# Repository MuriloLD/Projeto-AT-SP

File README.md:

# Projeto-AT-SP
Source code and instructions needed for constructing AntTruck and SuperTruck. Both mobile robots conected to Internet.

For more information please download the documentation [here](https://github.com/MuriloLD/Projeto-AT-SP/blob/master/Documenta%C3%A7%C3%A3o_Projeto_ATSP.pdf).

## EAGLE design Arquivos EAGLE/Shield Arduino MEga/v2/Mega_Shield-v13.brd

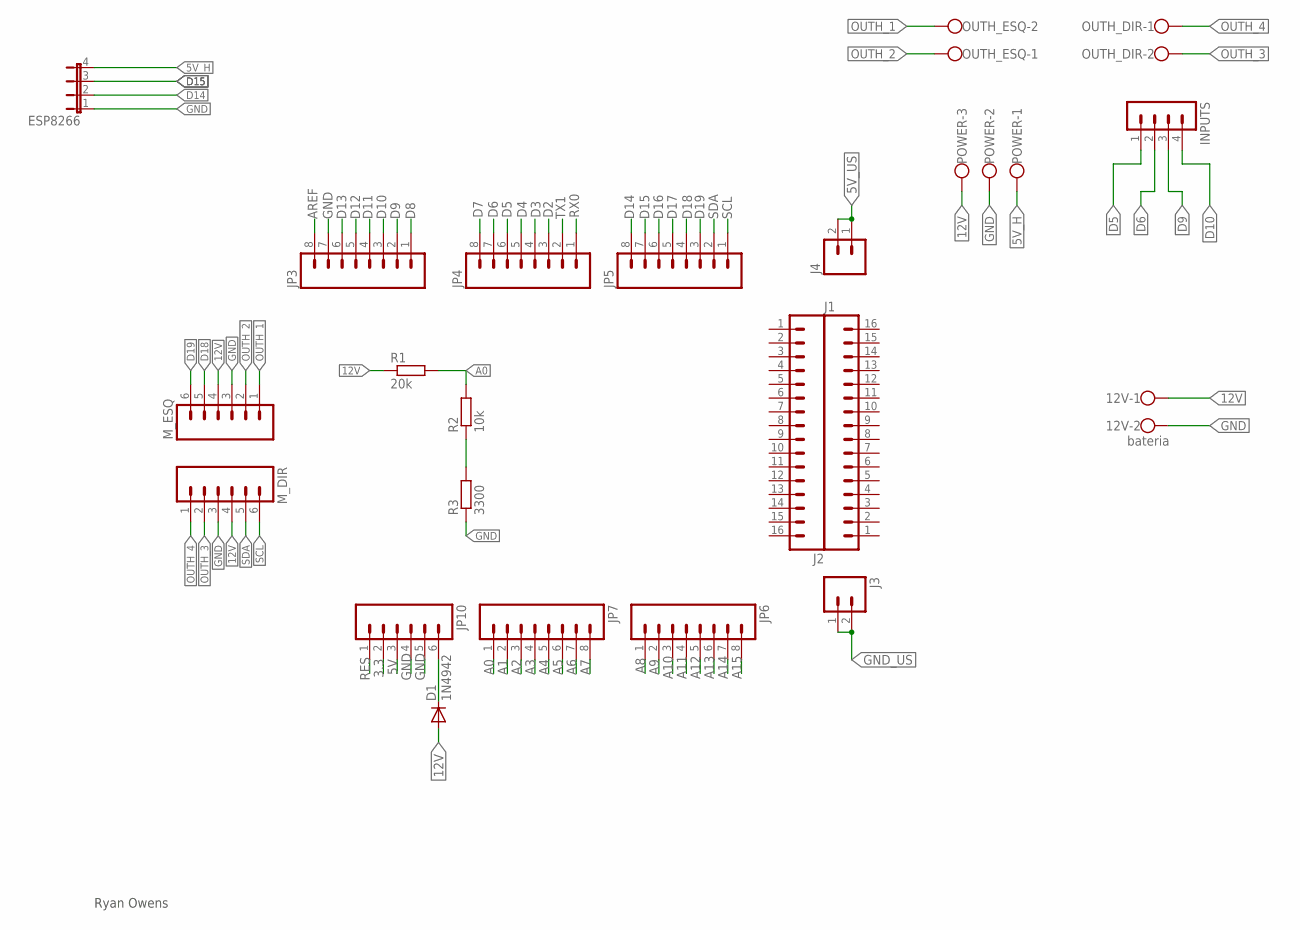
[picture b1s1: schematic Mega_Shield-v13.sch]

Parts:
12V: bateria; W237-102
D1: 1N4942; DO41-10
ESP8266: JP4E; JP4
INPUTS: MA04-1
J1, J2: M16LOCK; 1X16_LOCK
J3, J4: M02LOCK; 1X02_LOCK
JP3, JP4, JP5, JP6, JP7: M08LOCK; 1X08_LOCK
JP10: M06LOCK; 1X06_LOCK
M_DIR: M06LOCK; 1X06_LOCK
M_ESQ: M06LOCK; 1X06_LOCK
OUTH_DIR: W237-102
OUTH_ESQ: W237-102
POWER: W237-103
R1: 20k; 0207/10
R2: 10k; 0207/10
R3: 3300; 0207/10

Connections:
3.3: JP10.2
5V: JP10.3
5V_H: ESP8266.4, POWER.1
5V_US: J4.1, J4.2
12V: 12V.1, D1.A, M_DIR.4, M_ESQ.4, POWER.3, R1.1
A0: JP7.1, R1.2, R2.2
A1: JP7.2
A2: JP7.3
A3: JP7.4
A4: JP7.5
A5: JP7.6
A6: JP7.7
A7: JP7.8
A8: JP6.1
A9: JP6.2
A10: JP6.3
A11: JP6.4
A12: JP6.5
A13: JP6.6
A14: JP6.7
A15: JP6.8
AREF: JP3.8
D2: JP4.3
D3: JP4.4
D4: JP4.5
D5: INPUTS.1, JP4.6
D6: INPUTS.2, JP4.7
D7: JP4.8
D8: JP3.1
D9: INPUTS.3, JP3.2
D10: INPUTS.4, JP3.3
D11: JP3.4
D12: JP3.5
D13: JP3.6
D14: ESP8266.2, JP5.8
D15: ESP8266.3, JP5.7
D16: JP5.6
D17: JP5.5
D18: JP5.4, M_ESQ.5
D19: JP5.3, M_ESQ.6
GND: 12V.2, ESP8266.1, JP3.7, JP10.4, JP10.5, M_DIR.3, M_ESQ.3, POWER.2, R3.1
GND_US: J3.1, J3.2
unnamed: R2.1, R3.2
unnamed: D1.C, JP10.6
OUTH_1: M_ESQ.1, OUTH_ESQ.2
OUTH_2: M_ESQ.2, OUTH_ESQ.1
OUTH_3: M_DIR.2, OUTH_DIR.2
OUTH_4: M_DIR.1, OUTH_DIR.1
RES: JP10.1
RX0: JP4.1
SCL: JP5.1, M_DIR.6
SDA: JP5.2, M_DIR.5
TX1: JP4.2

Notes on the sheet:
Ryan Owens

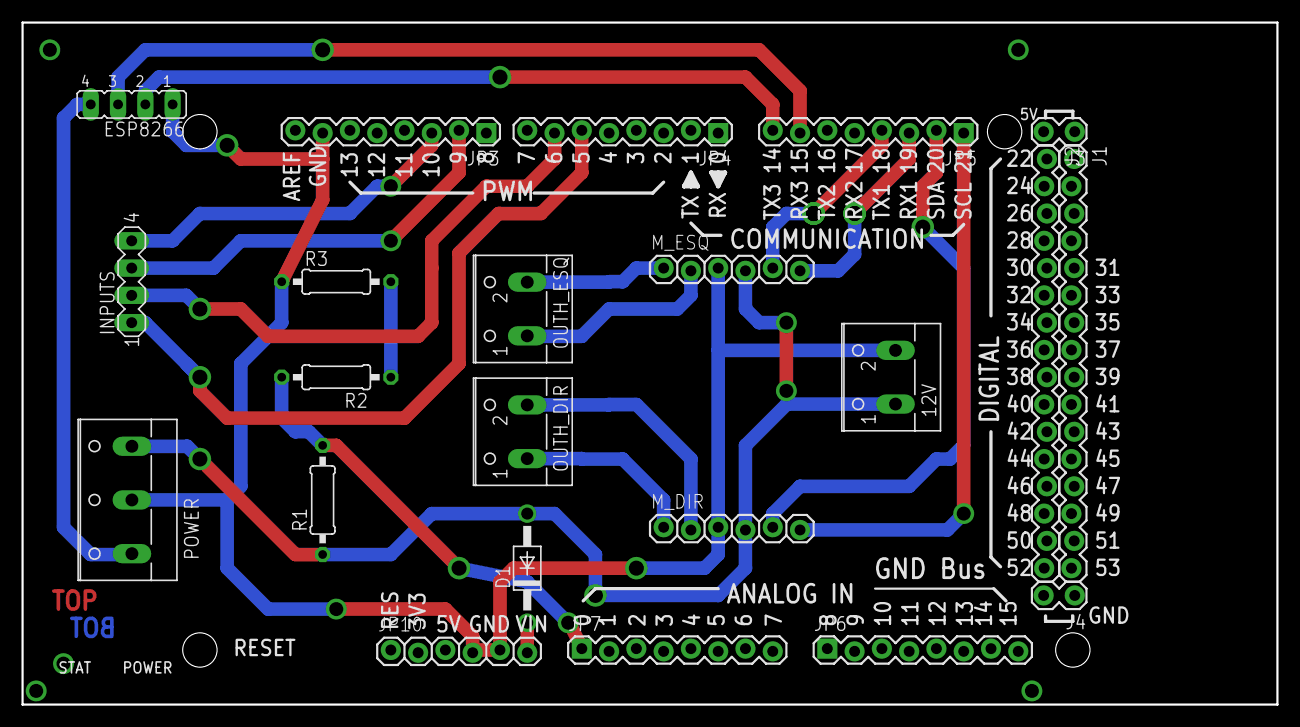
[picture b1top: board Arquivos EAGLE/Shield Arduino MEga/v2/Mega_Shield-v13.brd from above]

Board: 2 copper layers, 116.8 x 63.5 mm, 22 parts (0 on the bottom side), 22 nets.

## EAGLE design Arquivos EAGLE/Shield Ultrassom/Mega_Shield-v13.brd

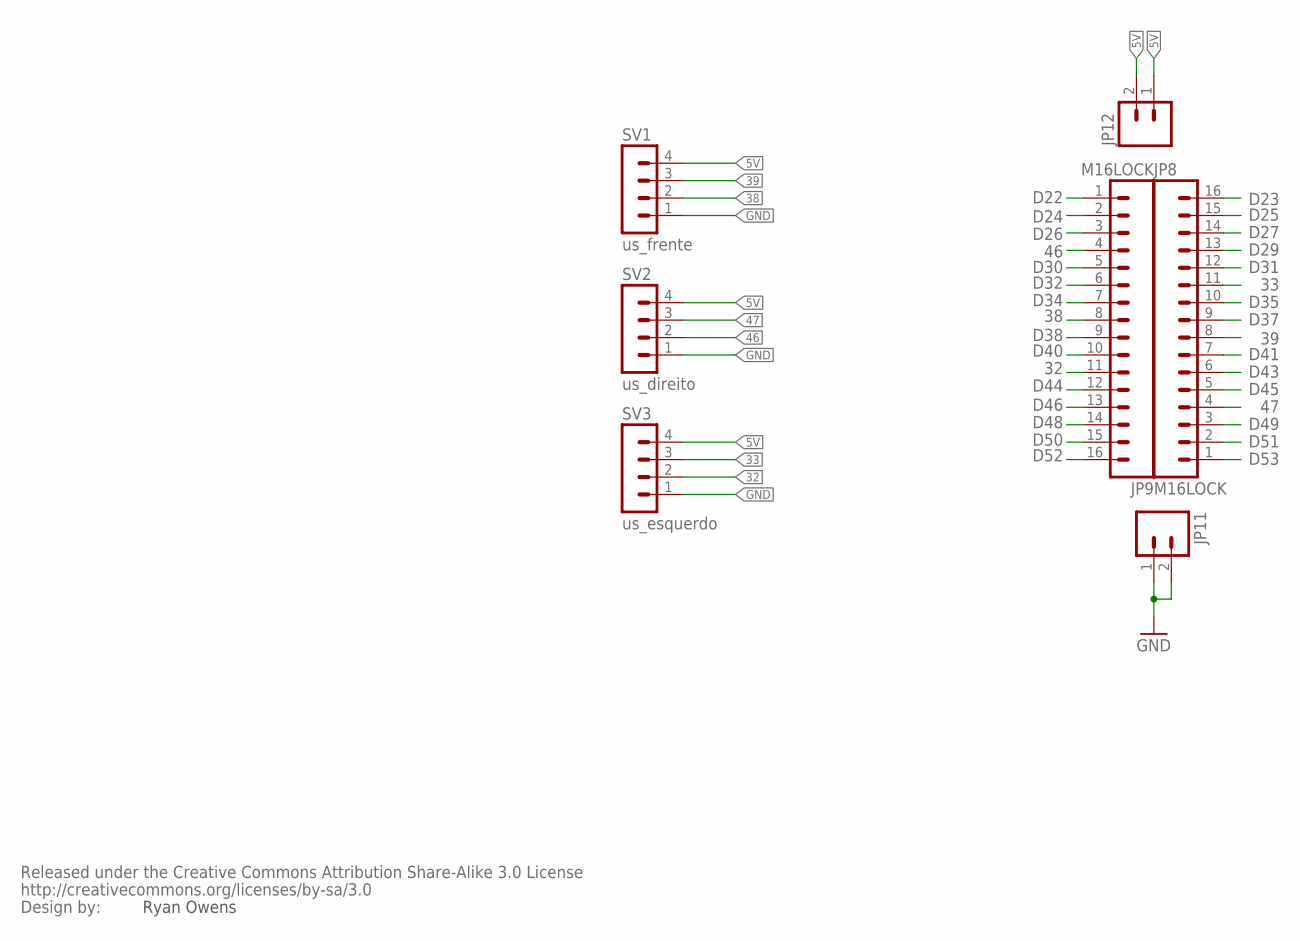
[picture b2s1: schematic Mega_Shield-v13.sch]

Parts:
JP8, JP9: M16LOCK; 1X16_LOCK
JP11, JP12: M02LOCK; 1X02_LOCK
SV1: us_frente; MA04-1
SV2: us_direito; MA04-1
SV3: us_esquerdo; MA04-1
U$2: CREATIVE_COMMONS

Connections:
5V: JP12.1, JP12.2, SV1.4, SV2.4, SV3.4
32: JP9.11, SV3.2
33: JP8.11, SV3.3
38: JP9.8, SV1.2
39: JP8.8, SV1.3
46: JP9.4, SV2.2
47: JP8.4, SV2.3
D22: JP9.1
D23: JP8.16
D24: JP9.2
D25: JP8.15
D26: JP9.3
D27: JP8.14
D29: JP8.13
D30: JP9.5
D31: JP8.12
D32: JP9.6
D34: JP9.7
D35: JP8.10
D37: JP8.9
D38: JP9.9
D40: JP9.10
D41: JP8.7
D43: JP8.6
D44: JP9.12
D45: JP8.5
D46: JP9.13
D48: JP9.14
D49: JP8.3
D50: JP9.15
D51: JP8.2
D52: JP9.16
D53: JP8.1
GND: JP11.1, JP11.2, SV1.1, SV2.1, SV3.1

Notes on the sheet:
Ryan Owens

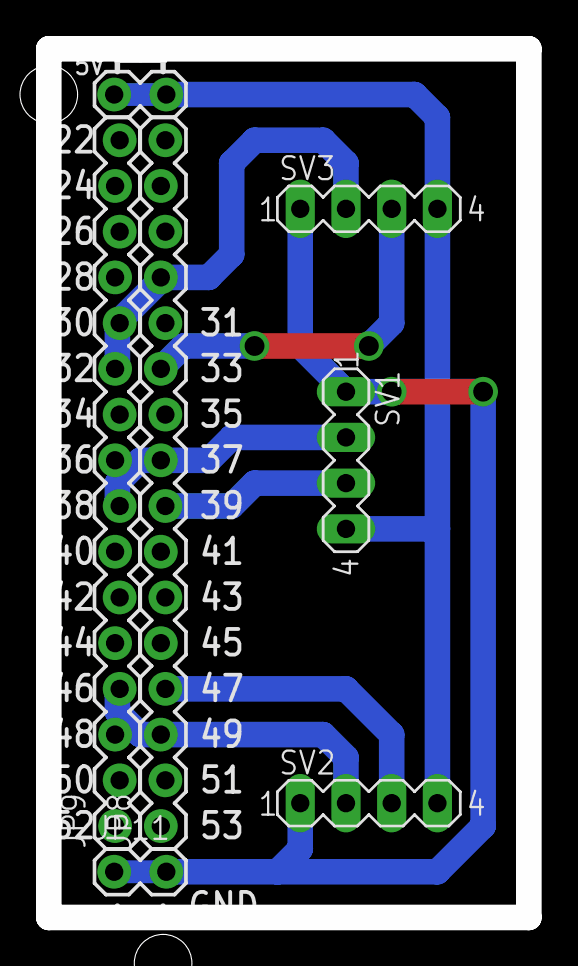
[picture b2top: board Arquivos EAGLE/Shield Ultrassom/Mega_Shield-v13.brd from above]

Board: 2 copper layers, 26.7 x 48.3 mm, 8 parts (0 on the bottom side), 8 nets.

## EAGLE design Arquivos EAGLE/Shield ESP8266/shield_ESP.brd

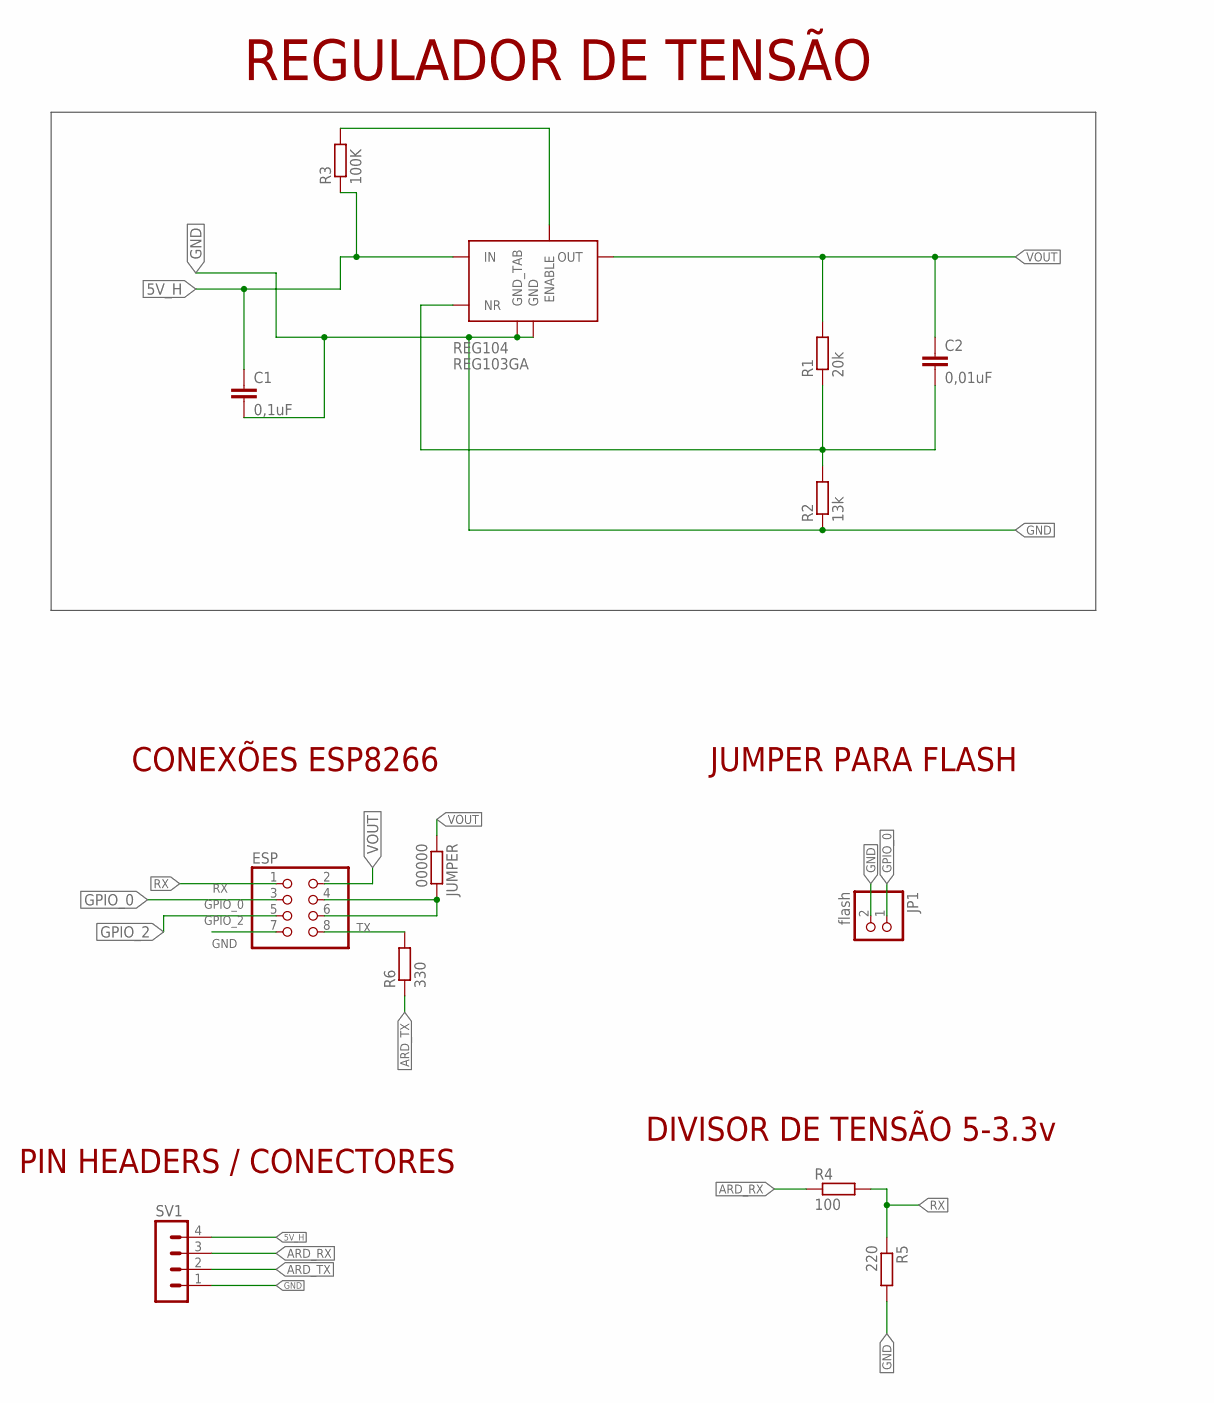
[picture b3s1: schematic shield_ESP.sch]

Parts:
C1: 0,1uF; C025-025X050
C2: 0,01uF; C025-025X050
ESP: PINHD-2X4; 2X04
JP1: flash; 1X02/90
JUMPER: 00000; 0207/7
R1: 20k; 0207/7
R2: 13k; 0207/7
R3: 100K; 0207/7
R4: 100; 0207/7
R5: 220; 0207/7
R6: 330; 0207/7
REG104: REG103GA; SOT223-5
SV1: MA04-1

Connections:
5V_H: C1.1, R3.1, REG104.1 (IN), SV1.4
ARD_RX: R4.1, SV1.3
ARD_TX: R6.1, SV1.2
GND: C1.2, ESP.7, JP1.2, R2.1, R5.2, REG104.3 (GND), REG104.TAB (GND_TAB), SV1.1
GPIO_0: ESP.3, JP1.1
GPIO_2: ESP.5
unnamed: ESP.4, ESP.6, JUMPER.2
unnamed: C2.2, R1.1, R2.2, REG104.4 (NR)
unnamed: R3.2, REG104.5 (ENABLE)
RX: ESP.1, R4.2, R5.1
TX: ESP.8, R6.2
VOUT: C2.1, ESP.2, JUMPER.1, R1.2, REG104.2 (OUT)

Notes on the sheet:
REGULADOR DE TENSÃO
PIN HEADERS / CONECTORES
DIVISOR DE TENSÃO 5-3.3v
CONEXÕES ESP8266
JUMPER PARA FLASH

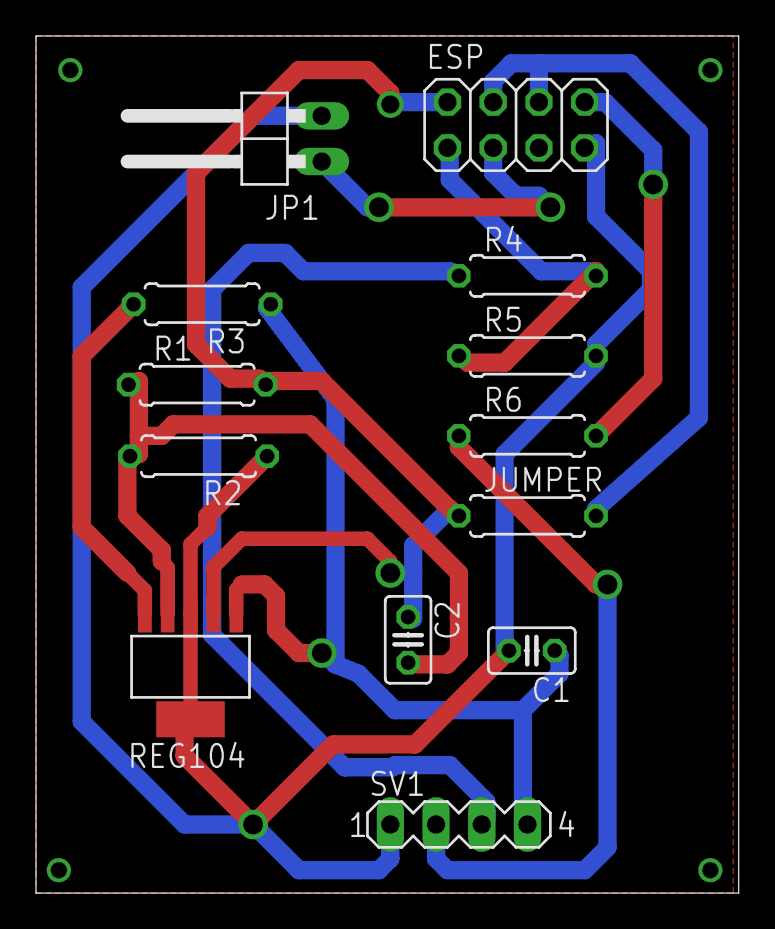
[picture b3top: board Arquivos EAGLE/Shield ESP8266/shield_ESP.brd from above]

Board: 2 copper layers, 39.0 x 47.6 mm, 13 parts (0 on the bottom side), 11 nets.

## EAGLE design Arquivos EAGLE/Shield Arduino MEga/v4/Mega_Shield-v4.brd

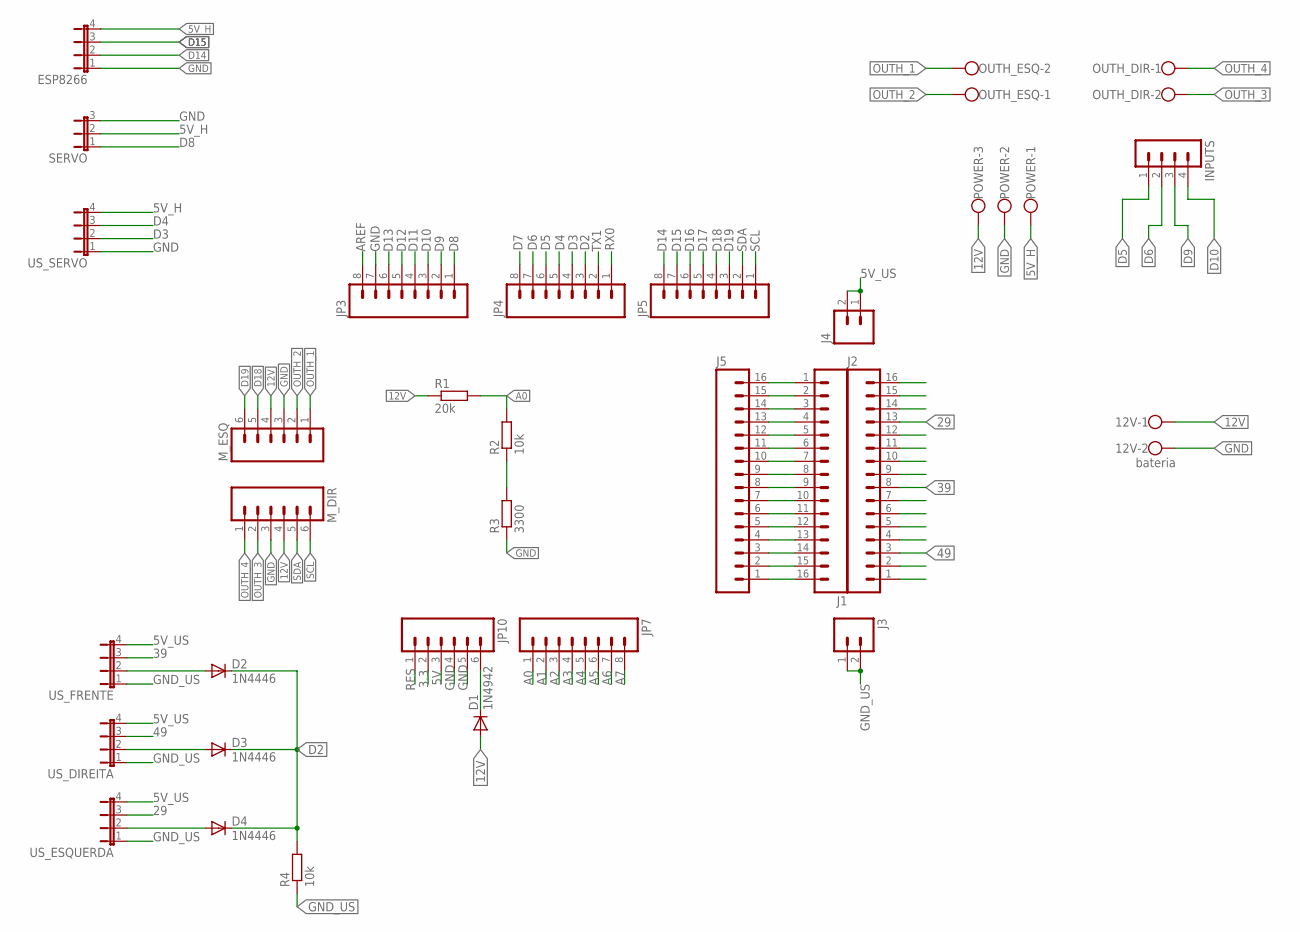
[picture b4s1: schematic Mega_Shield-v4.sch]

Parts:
12V: bateria; W237-102
D1: 1N4942; DO41-10
D2, D3, D4: 1N4446; DO35-10
ESP8266: JP4E; JP4
INPUTS: MA04-1
J1, J2, J5: M16LOCK; 1X16_LOCK
J3, J4: M02LOCK; 1X02_LOCK
JP3, JP4, JP5, JP7: M08LOCK; 1X08_LOCK
JP10: M06LOCK; 1X06_LOCK
M_DIR: M06LOCK; 1X06_LOCK
M_ESQ: M06LOCK; 1X06_LOCK
OUTH_DIR: W237-102
OUTH_ESQ: W237-102
POWER: W237-103
R1: 20k; 0207/10
R2, R4: 10k; 0207/10
R3: 3300; 0207/10
SERVO: JP2W
US_DIREITA: JP4E; JP4
US_ESQUERDA: JP4E; JP4
US_FRENTE: JP4E; JP4
US_SERVO: JP4E; JP4

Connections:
3.3: JP10.2
5V: JP10.3
5V_H: ESP8266.4, POWER.1, SERVO.2, US_SERVO.4
5V_US: J4.1, J4.2, US_DIREITA.4, US_ESQUERDA.4, US_FRENTE.4
12V: 12V.1, D1.A, M_DIR.4, M_ESQ.4, POWER.3, R1.1
29: J2.13, US_ESQUERDA.3
39: J2.8, US_FRENTE.3
49: J2.3, US_DIREITA.3
A0: JP7.1, R1.2, R2.2
A1: JP7.2
A2: JP7.3
A3: JP7.4
A4: JP7.5
A5: JP7.6
A6: JP7.7
A7: JP7.8
AREF: JP3.8
D2: D2.C, D3.C, D4.C, JP4.3, R4.2
D3: JP4.4, US_SERVO.2
D4: JP4.5, US_SERVO.3
D5: INPUTS.1, JP4.6
D6: INPUTS.2, JP4.7
D7: JP4.8
D8: JP3.1, SERVO.1
D9: INPUTS.3, JP3.2
D10: INPUTS.4, JP3.3
D11: JP3.4
D12: JP3.5
D13: JP3.6
D14: ESP8266.2, JP5.8
D15: ESP8266.3, JP5.7
D16: JP5.6
D17: JP5.5
D18: JP5.4, M_ESQ.5
D19: JP5.3, M_ESQ.6
GND: 12V.2, ESP8266.1, JP3.7, JP10.4, JP10.5, M_DIR.3, M_ESQ.3, POWER.2, R3.1, SERVO.3, US_SERVO.1
GND_US: J3.1, J3.2, R4.1, US_DIREITA.1, US_ESQUERDA.1, US_FRENTE.1
unnamed: R2.1, R3.2
unnamed: D1.C, JP10.6
unnamed: D2.A, US_FRENTE.2
unnamed: J1.16, J5.1
unnamed: D3.A, US_DIREITA.2
unnamed: J1.15, J5.2
unnamed: J1.14, J5.3
unnamed: J1.13, J5.4
unnamed: D4.A, US_ESQUERDA.2
unnamed: J1.12, J5.5
unnamed: J1.11, J5.6
unnamed: J1.10, J5.7
unnamed: J1.9, J5.8
unnamed: J1.8, J5.9
unnamed: J1.7, J5.10
unnamed: J1.6, J5.11
unnamed: J1.5, J5.12
unnamed: J1.4, J5.13
unnamed: J1.3, J5.14
unnamed: J1.2, J5.15
unnamed: J1.1, J5.16
OUTH_1: M_ESQ.1, OUTH_ESQ.2
OUTH_2: M_ESQ.2, OUTH_ESQ.1
OUTH_3: M_DIR.2, OUTH_DIR.2
OUTH_4: M_DIR.1, OUTH_DIR.1
RES: JP10.1
RX0: JP4.1
SCL: JP5.1, M_DIR.6
SDA: JP5.2, M_DIR.5
TX1: JP4.2

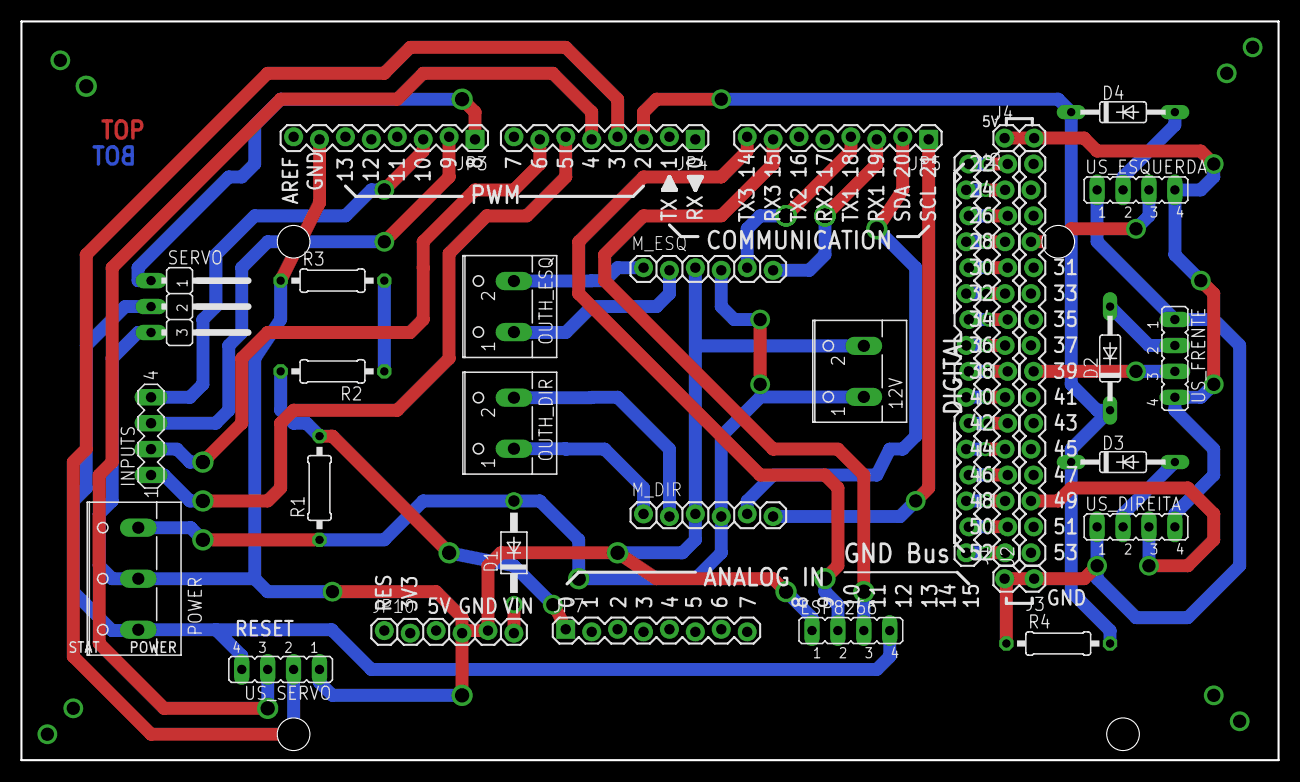
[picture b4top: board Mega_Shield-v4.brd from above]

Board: 2 copper layers, 123.2 x 72.4 mm, 31 parts (0 on the bottom side), 48 nets.

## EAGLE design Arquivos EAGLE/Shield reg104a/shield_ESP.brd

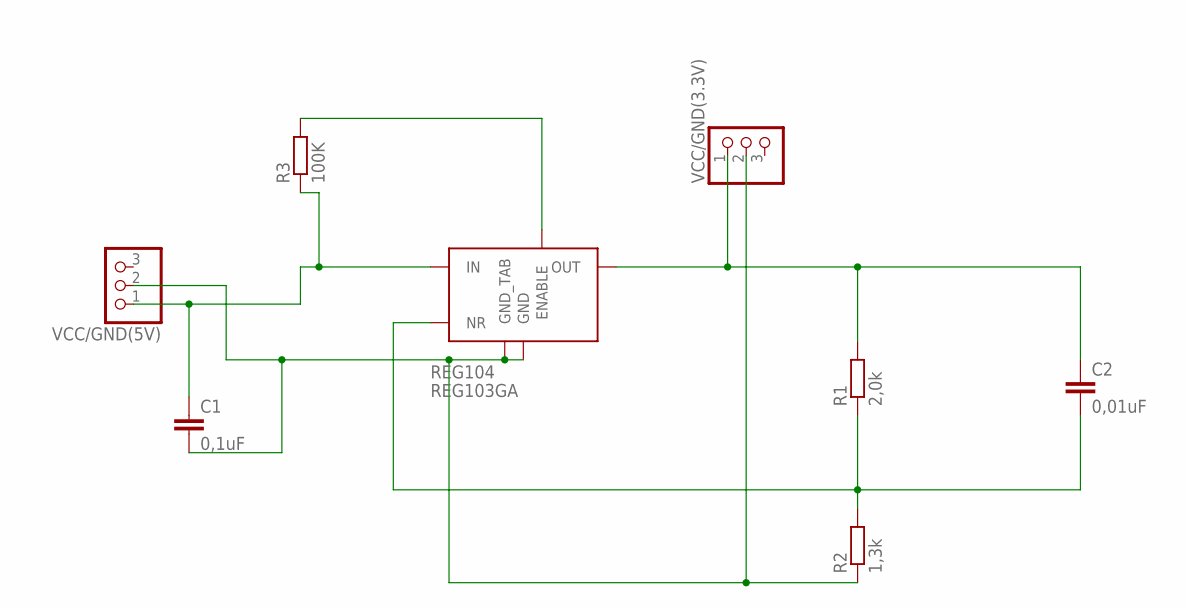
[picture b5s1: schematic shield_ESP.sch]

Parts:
C1: 0,1uF; C025-025X050
C2: 0,01uF; C025-025X050
R1: 2,0k; 0207/7
R2: 1,3k; 0207/7
R3: 100K; 0207/7
REG104: REG103GA; SOT223-5
VCC/GND(3.3V), VCC/GND(5V): PINHD-1X3/90; 1X03/90

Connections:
GOUT: C1.2, R2.1, REG104.3 (GND), REG104.TAB (GND_TAB), VCC/GND(3.3V).2, VCC/GND(5V).2
unnamed: C1.1, R3.1, REG104.1 (IN), VCC/GND(5V).1
unnamed: C2.2, R1.1, R2.2, REG104.4 (NR)
unnamed: R3.2, REG104.5 (ENABLE)
VOUT: C2.1, R1.2, REG104.2 (OUT), VCC/GND(3.3V).1

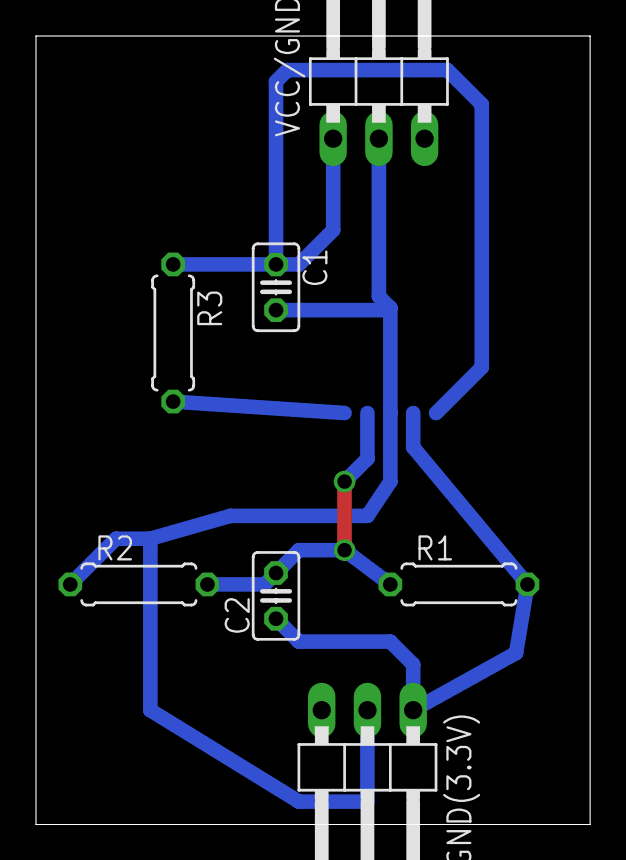
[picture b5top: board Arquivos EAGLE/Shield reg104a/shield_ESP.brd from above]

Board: 2 copper layers, 30.8 x 43.8 mm, 8 parts (1 on the bottom side), 5 nets.

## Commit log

2016-11-08 Updating README
    Testing Commit changes.
2016-11-09 Adicionando arquivo .gitignore
2016-11-09 Including SuperTruck codes and Eagle files
2016-11-09 Including all other files
2016-11-10 Updating MeteorJS files and adding personalized NodeMCU firmware
2017-01-09 Updates...
2017-01-10 Changes in Eagle boards and Arduino libraries
2017-01-12 3D Parts Dimensions Added.
2017-01-16 Foders organized and renamed.
2017-01-17 Minor changes.
2017-01-23 Variables' names changed.
2017-01-24 Bug fixes.
2017-01-24 Code adjustments.
2017-01-30 Comments improved.
2017-02-01 Documentation.
2017-02-01 gitignore
2017-02-03 Documentation
2017-03-10 fixed bugs
2017-03-22 setPose added.
2017-03-22 Changed uart setup.
2017-03-22 Added setPID by mqtt method
2017-04-12 ESP8266 codes updated.
2017-04-18 IS docoding vars added.
2017-07-11 Update NodeMCU codes.
2017-07-11 Image added.
2017-07-11 Send vars to Arduino period changed.

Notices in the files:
parts and their libraries:
SparkFun-Connectors: Licensing: Creative Commons ShareAlike 4.0 International - https://creativecommons.org/licenses/by-sa/4.0
SparkFun: Released under the Creative Commons Attribution Share-Alike 3.0 License
SparkFun: http://creativecommons.org/licenses/by-sa/3.0
